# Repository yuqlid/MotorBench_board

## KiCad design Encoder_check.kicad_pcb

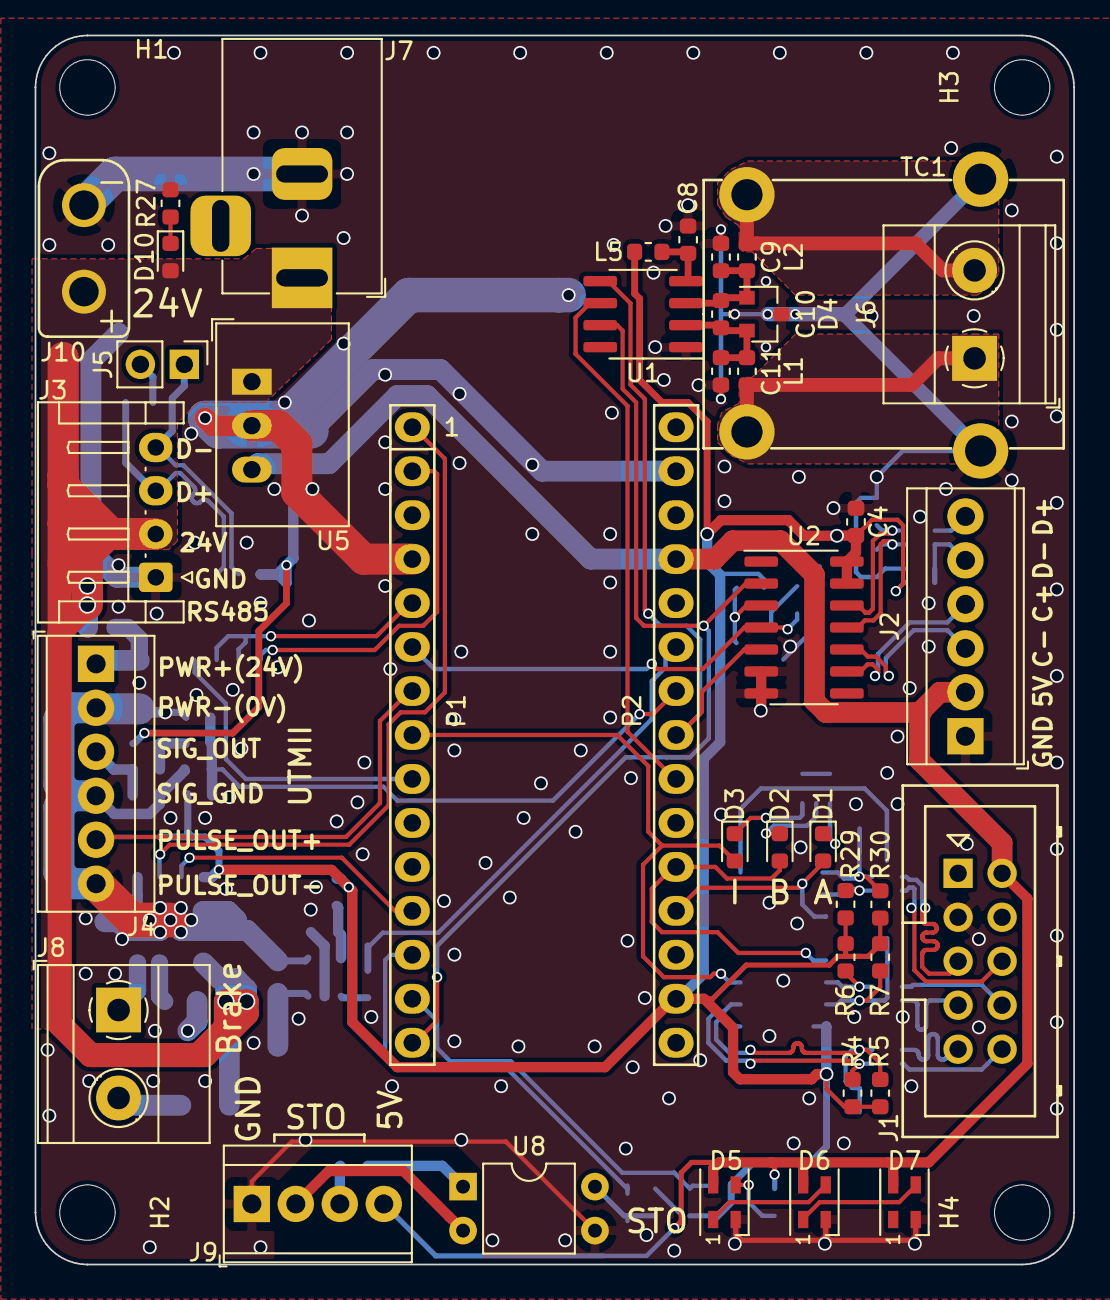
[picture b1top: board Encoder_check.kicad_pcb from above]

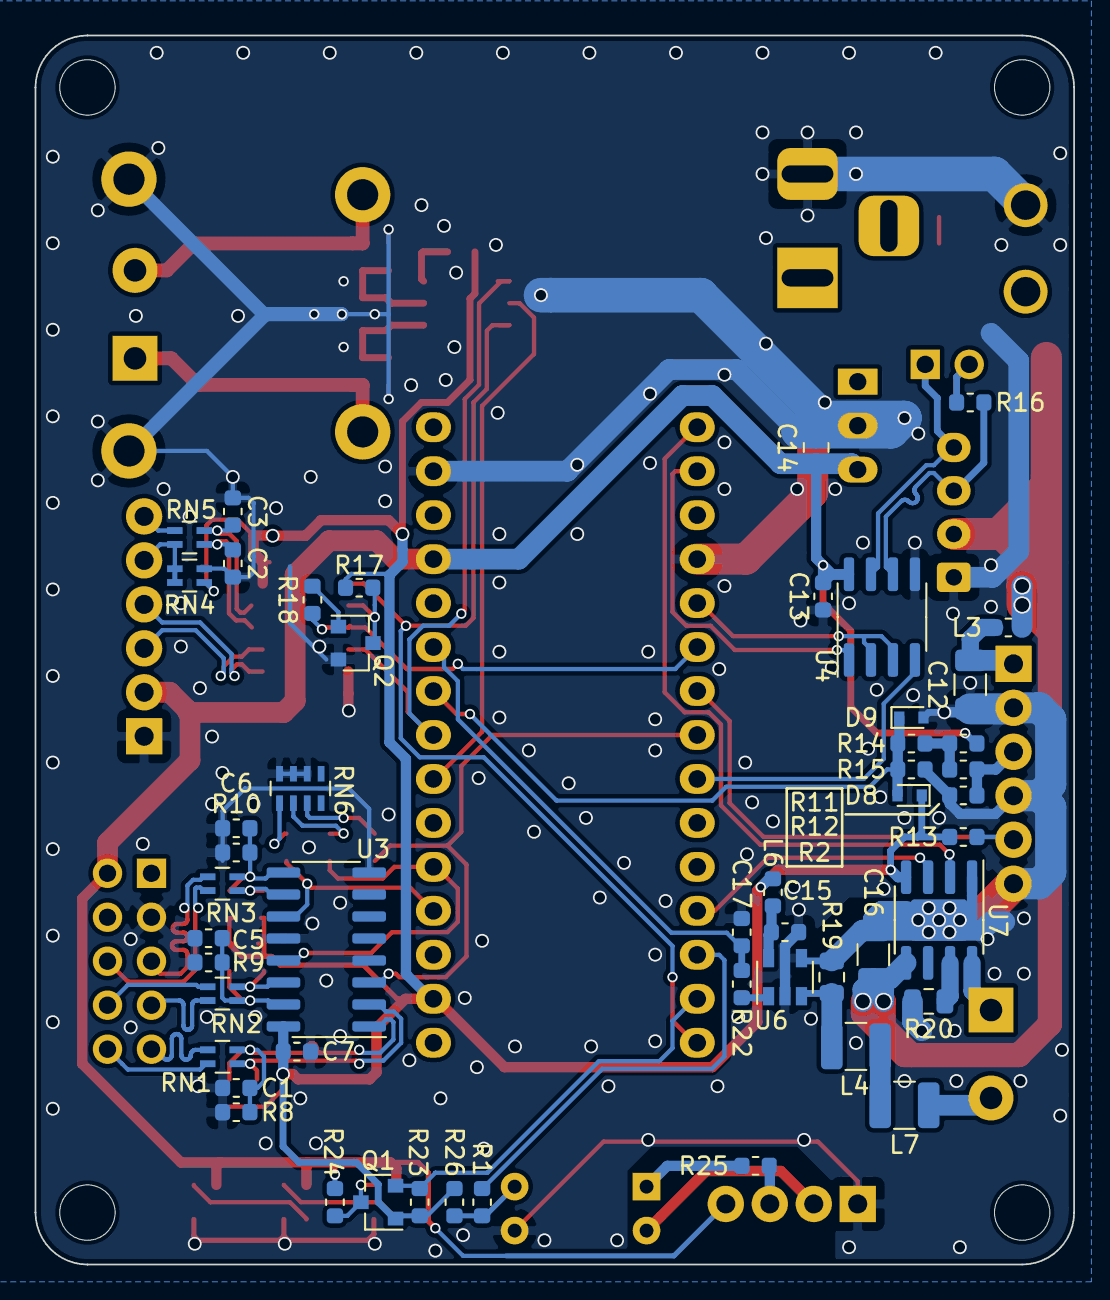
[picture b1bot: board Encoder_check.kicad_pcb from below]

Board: 2 copper layers, 60.0 x 71.0 mm, 94 parts (50 on the bottom side), 71 nets.

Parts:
C1, C2, C3, C5, C6: 220p; C_0603_1608Metric
C4, C7, C8, C13, C15, C17: 0.1u; C_0603_1608Metric
C9, C11: DNP; C_0603_1608Metric
C10: 10n; C_0603_1608Metric
C12: C; C_1206_3216Metric
C14: 3.3u; C_0805_2012Metric
C16: 1u; C_1206_3216Metric
D1, D2, D3, D10: LED; LED_0603_1608Metric
D4: D_TVS_x2_AAC; SOT-23
D5, D6, D7: SK6805; LED_SK6805_PLCC4_2.4x2.7mm_P1.3mm
D8, D9: D; D_SOD-523
H1, H2, H3, H4: MountingHole; MountingHole_3.2mm_M3
J1: Conn_02x05_Odd_Even; Multicomp_MC9A12-1034_2x05_P2.54mm_Vertical
J2, J4: Screw_Terminal_01x06; TerminalBlock_TE_282834-6_1x06_P2.54mm_Horizontal
J3: Conn_01x04; JST_EH_S4B-EH_1x04_P2.50mm_Horizontal
J5: Conn_01x02; PinHeader_1x02_P2.54mm_Vertical
J6, J8: Screw_Terminal_01x02; TerminalBlock_Phoenix_MKDS-1,5-2-5.08_1x02_P5.08mm_Horizont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
J7: Barrel_Jack_Switch; BarrelJack_Horizontal
J9: Screw_Terminal_01x04; TerminalBlock_TE_282834-4_1x04_P2.54mm_Horizontal
J10: Conn_01x02; XT30PB
L1, L2, L3, L5, L6: L; L_0603_1608Metric
L4, L7: L; L_1210_3225Metric
P1: Digital; Socket_Strip_Arduino_1x15
P2: Analog; Socket_Strip_Arduino_1x15
Q1, Q2: BSS138; SOT-23
R1, R13, R18, R25: 1k; R_0603_1608Metric
R2, R4, R6, R11, R12, R14, R15, R17, R23, R24, R26, R29: 10k; R_0603_1608Metric
R5, R7, R8, R9, R10, R27, R30: 20k; R_0603_1608Metric
R16: 120; R_0603_1608Metric
R19: 0.05; L_0805_2012Metric
R20: 0; L_0805_2012Metric
R22: 100; L_0603_1608Metric
RN1, RN2, RN3, RN5: 150; R_Array_Concave_2x0603
RN4: 4.7k; R_Array_Concave_2x0603
RN6: 1k; R_Array_Concave_4x0603
TC1: Thermocouple_PCB; Omega_PCC-SMP_1x2_P13.70mm_Horizontal
U1: MAX31855KASA; SOIC-8_3.9x4.9mm_P1.27mm
U2: ISL83491; SOIC-14_3.9x8.7mm_P1.27mm
U3: AM26LV32xD; SOIC-16_3.9x9.9mm_P1.27mm
U4: ST485BDR; SOIC-8_3.9x4.9mm_P1.27mm
U5: M78AR05-1; Converter_DCDC_MINIMAX_M78AR05-1_THT
U6: INA180A; SOT-23-5
U7: A4953_LJ; SOIC-8-1EP_3.9x4.9mm_P1.27mm_EP2.41x3.3mm
U8: TLP785; DIP-4_W7.62mm

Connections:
+3V3: C4.1, C7.1, D8.1, L5.1, L6.1, P2.14, Q1.1, R4.1, R5.1, R6.1, R7.1, R13.2, R17.2, R23.1, R26.1, R29.1, R30.1, RN4.3, U2.13, U2.14, U3.16, U7.4
+5V: C13.1, C14.1, D5.4, D6.4, D7.4, J1.2, J2.2, J9.4, P2.4, R11.1, R24.1, U4.8, U5.3
+24V: C16.1, D10.2, J3.2, J7.1, J10.1, L3.2, U5.1, U7.5
/0(Rx): P1.2, U4.1
/1(Tx): P1.1, U7.2
/2: P1.5, U4.2, U4.3
/3(**): P1.6, R18.1, U2.4
/4: J4.5, P1.7, R13.1
/5(**): D3.2, P1.8, U3.3
/6(**): P1.9, U4.4
/9(**): P1.12, U7.3
/10(**/SS): P1.13, R1.1
/11(**/MOSI): P1.14, Q1.2, R23.2
/12(MISO): P1.15, U1.7, U2.2
/A0: D1.2, P2.12, U3.11
/A1: D2.2, P2.11, U3.13
/A3: P2.9, U1.6
/A4: P2.8, U1.5, U2.5
/A5: D8.2, D9.1, P2.7, R14.1, R15.2
/A6: C17.1, P2.6, R22.1
/Reset: P1.3, P2.3
/brake/brake_+: J8.1, U7.8
/brake/brake_-: J8.2, L7.1
/inc_encoder/A+: J1.6, RN3.4
/inc_encoder/A-: J1.5, RN3.3
/inc_encoder/A_+: R29.2, RN3.1, U3.10
/inc_encoder/A_-: C6.1, R10.1, R30.2, RN3.2, U3.9
/inc_encoder/B+: J1.8, RN2.3
/inc_encoder/B-: J1.7, RN2.4
/inc_encoder/B_+: R6.2, RN2.2, U3.14
/inc_encoder/B_-: C5.1, R7.2, R9.1, RN2.1, U3.15
/inc_encoder/I+: J1.10, RN1.4
/inc_encoder/I-: J1.9, RN1.3
/inc_encoder/I_+: R4.2, RN1.1, U3.2
/inc_encoder/I_-: C1.1, R5.2, R8.1, RN1.2, U3.1
/rs485/RS485_+: J3.3, R16.2, U4.6
/rs485/RS485_-: J3.4, J5.1, U4.7
/ssi_encoder/C_+: J2.4, U2.9
/ssi_encoder/C_-: J2.3, U2.10
/ssi_encoder/D_+: J2.6, RN5.3
/ssi_encoder/D_-: J2.5, RN4.1, RN4.2, RN5.4
/ssi_encoder/Dout_+: C3.1, RN5.2, U2.12
/ssi_encoder/Dout_-: C2.1, RN5.1, U2.11
/thermocouple/T+: J6.2, L2.1, TC1.1
/thermocouple/T-: J6.1, L1.1, TC1.2
/utm/PWR+(24V): C12.1, J4.1, L3.1
/utm/SIG_OUT: J4.3, R2.2, R12.1
GND: C1.2, C2.2, C3.2, C4.2, C5.2, C6.2, C7.2, C8.2, C9.1, C11.2, C12.2, C13.2, C14.2, C15.2, C16.2, C17.2, D4.3, D5.2, D6.2, D7.2, D9.2, J1.3, J2.1, J3.1, J4.2, J4.4, J4.6, J7.2, J9.1, J10.2, P1.4, P2.2, Q2.2, R2.1, R8.2, R9.2, R10.2, R15.1, R19.2, R20.2, R27.2, RN4.4, RN6.6, RN6.7, RN6.8, TC1.3, U1.1, U2.6, U2.7, U3.4, U3.8, U3.12, U4.5, U5.2, U6.2, U6.4, U7.1, U7.9, U8.3
unnamed: C8.1, L5.2, U1.4
unnamed: C9.2, C10.1, D4.1, L2.2, U1.3
unnamed: C10.2, C11.1, D4.2, L1.2, U1.2
unnamed: C15.1, L6.2, U6.5
unnamed: D1.1, RN6.1
unnamed: D2.1, RN6.2
unnamed: D3.1, RN6.3
unnamed: D5.1, D6.3
unnamed: D5.3, Q1.3, R24.2
unnamed: D6.1, D7.3
unnamed: D10.1, R27.1
unnamed: J5.2, R16.1
unnamed: J9.2, U8.2
unnamed: J9.3, R25.2
unnamed: L4.1, L7.2
unnamed: L4.2, R19.1, U6.3
unnamed: Q2.1, R18.2
unnamed: Q2.3, R17.1, U2.3
unnamed: R1.2, R26.2, U8.4
unnamed: R11.2, R12.2, R14.2
unnamed: R20.1, U7.7
unnamed: R22.2, U6.1
unnamed: R25.1, U8.1

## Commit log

2020-02-13 これで発注
2020-02-13 Create LICENSE
2020-02-22 SPIにつなぐデバイスの電圧が違ったため設計ミスが判明。 これを修正した
2020-02-23 見つけた設計ミスを全部反映
2020-02-25 部品のパラメータ未記入部分があったので追記
2020-03-28 エンコーダの配線ミスってた
2020-03-29 レシーバの出力が有効になっていないとうアホなミスを修正
2020-04-04 設計修正
2020-04-29 シルクミスやらかした
